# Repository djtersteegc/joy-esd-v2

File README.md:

ESD Protection for Atari/Commodore style DB9 joystick ports. If manufacturing your own PCB's, use a thinner option like 0.6mm, instead of the default 1.6mm as you will be installing these on the back side of your computer's mainboard so you want to minimize the height here.

I assembled mine with LiteON L13ESDL5V0C6-4 TVS diodes, but any SOT-23-6 package with a 5V standoff voltage should do the job.  A common base part number here is SRV05-4.

Here's a shot installed on a C64.

Inspired by the work at https://www.hackup.net/2020/08/esd-protection-for-the-c64-control-ports/

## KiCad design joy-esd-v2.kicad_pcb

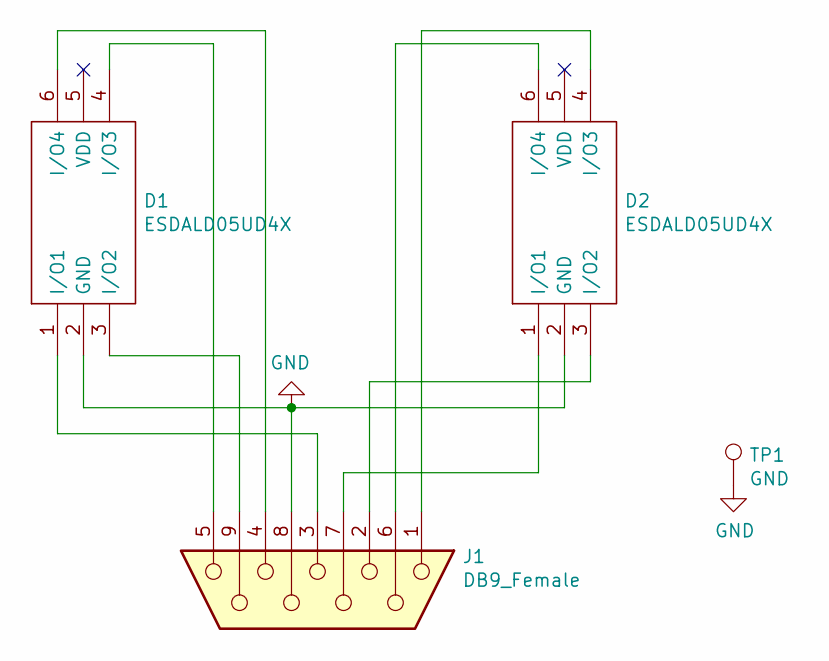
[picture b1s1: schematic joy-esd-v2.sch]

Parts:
D1, D2: ESDALD05UD4X; SOT95P280X125-6N; Mouser Part Number 771-ESDALD05UD4X
J1: DB9_Female; DSUB-9_Female_Vertical_P2.77x2.84mm
TP1: GND; SolderWirePad_1x01_SMD_1x2mm

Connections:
GND: D1.2 (GND), D2.2 (GND), J1.8, TP1.1
unnamed: D1.1 (I/O1), J1.3
unnamed: D1.3 (I/O2), J1.9
unnamed: D1.4 (I/O3), J1.5
unnamed: D1.6 (I/O4), J1.4
unnamed: D2.1 (I/O1), J1.7
unnamed: D2.3 (I/O2), J1.2
unnamed: D2.4 (I/O3), J1.1
unnamed: D2.6 (I/O4), J1.6

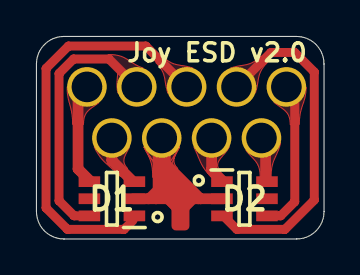
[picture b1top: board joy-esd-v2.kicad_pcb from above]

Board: 2 copper layers, 16.0 x 11.3 mm, 4 parts (0 on the bottom side), 9 nets.

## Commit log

2021-02-27 Initial release
2022-04-02 Move from 5 to 6 pin SOT-23 diodes
2022-04-17 Add teardrops and ibom
2023-11-05 Add some pics
2023-11-05 Update pics
2023-11-05 Add LiteON TVS datasheet
